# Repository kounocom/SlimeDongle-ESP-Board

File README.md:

# USB receiver for ESP-based SlimeVR trackers

## Notes:

 - Firmware won't be mine, not responsible for that

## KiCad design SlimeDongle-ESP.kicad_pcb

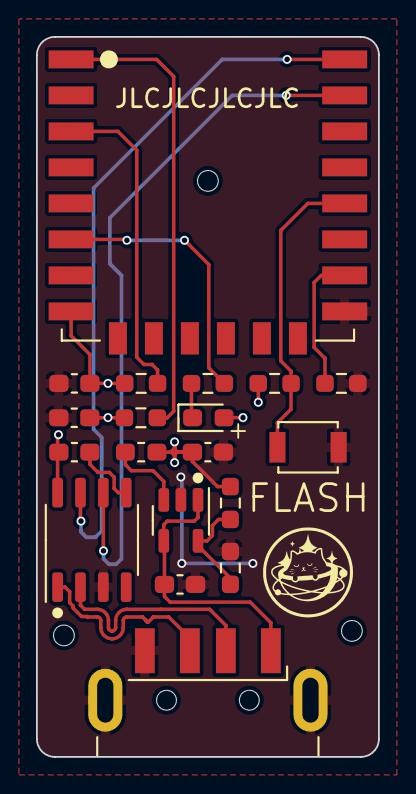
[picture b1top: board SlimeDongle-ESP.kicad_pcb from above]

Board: 2 copper layers, 19.0 x 40.0 mm, 19 parts (0 on the bottom side), 16 nets.

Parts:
C1, C5: 4u7; C_0603_1608Metric_Pad1.08x0.95mm_HandSolder
C2, C4: 100n; C_0603_1608Metric_Pad1.08x0.95mm_HandSolder
C3: 10u; C_0603_1608Metric_Pad1.08x0.95mm_HandSolder
D1: WHITE; LED_0603_1608Metric_Pad1.05x0.95mm_HandSolder
J1: USB_A; USB_A_CNCTech_1001-011-01101_Horizontal
L1: 2u2; L_0603_1608Metric_Pad1.05x0.95mm_HandSolder
R1: 40k; R_0603_1608Metric_Pad0.98x0.95mm_HandSolder
R2, R3, R4, R5, R6, R7: 10k; R_0603_1608Metric_Pad0.98x0.95mm_HandSolder
SW1: FLASH; SW_SPST_B3U-1000P
U1: M3406; SOT-23-5
U2: SOP-8_3.9x4.9mm_P1.27mm
U3: ESP-12F; ESP-12E

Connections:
+3V3: C2.1, C3.1, C4.2, C5.2, D1.2 (A), L1.2, R1.1, R3.1, R4.1, R7.1, U2.8 (V3), U3.8 (VCC)
+5V: C1.1, J1.1 (VBUS), U1.1 (RUN), U1.4 (VIN)
D+: J1.3 (D+), U2.1 (UD+)
D-: J1.2 (D-), U2.2 (UD-)
GND: C1.2, C3.2, C4.1, C5.1, J1.4 (GND), J1.5 (Shield), R2.2, R6.2, SW1.2 (B), U1.2 (GND), U2.3 (GND), U3.15 (GND)
unnamed: D1.1 (K), R5.1
unnamed: R7.2, SW1.1 (A), U3.18 (GPIO0)
unnamed: R1.2, R2.1, U1.5 (FB)
unnamed: L1.1, U1.3 (SW)
unnamed: C2.2, U2.5 (VCC)
unnamed: R3.2, U3.3 (EN)
unnamed: R5.2, U3.6 (GPIO12)
unnamed: R6.1, U3.16 (GPIO15)
unnamed: R4.2, U3.1 (~RST)
UART_RX: U2.7 (RXD), U3.22 (GPIO1/TXD)
UART_TX: U2.6 (TXD), U3.21 (GPIO3/RXD)

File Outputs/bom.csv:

Designator,Footprint,Quantity,Value,LCSC Part #
"C1, C5",0603,2,4u7,
"C2, C4",0603,2,100n,
C3,0603,1,10u,
D1,0603,1,WHITE,
J1,USB_A_CNCTech_1001-011-01101_Horizontal,1,USB_A,
L1,0603,1,2u2,
R1,0603,1,40k,
"R2, R3, R4, R5, R6, R7",0603,6,10k,
SW1,SW_SPST_B3U-1000P,1,FLASH,
U1,SOT-23-5,1,M3406,C83224
U2,SOP-8_3.9x4.9mm_P1.27mm,1,~,
U3,ESP-12E,1,ESP-12F,

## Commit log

2023-10-03 init
2023-10-03 added jlc pcba tooling holes
2023-11-07 fuck
2023-11-07 bom was fucky
